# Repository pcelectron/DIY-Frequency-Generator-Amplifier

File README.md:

# DIY-Frequency-Generator-Amplifier

This is a open source frequency generator amplifier capable of delivering up to 1.5 Amps and 28 Vpp at up to 100MHz. It is based on three THS3491 IC's in parallel. The gain of the amplifier stage is fixed at 2, but can be changed by changing the feedback network resistors.
This Repo has the Kicad project files, gerbers, BOM and 3d models of the board and case. Please make a pull request if you have imporvements, which you find to be useful for others.

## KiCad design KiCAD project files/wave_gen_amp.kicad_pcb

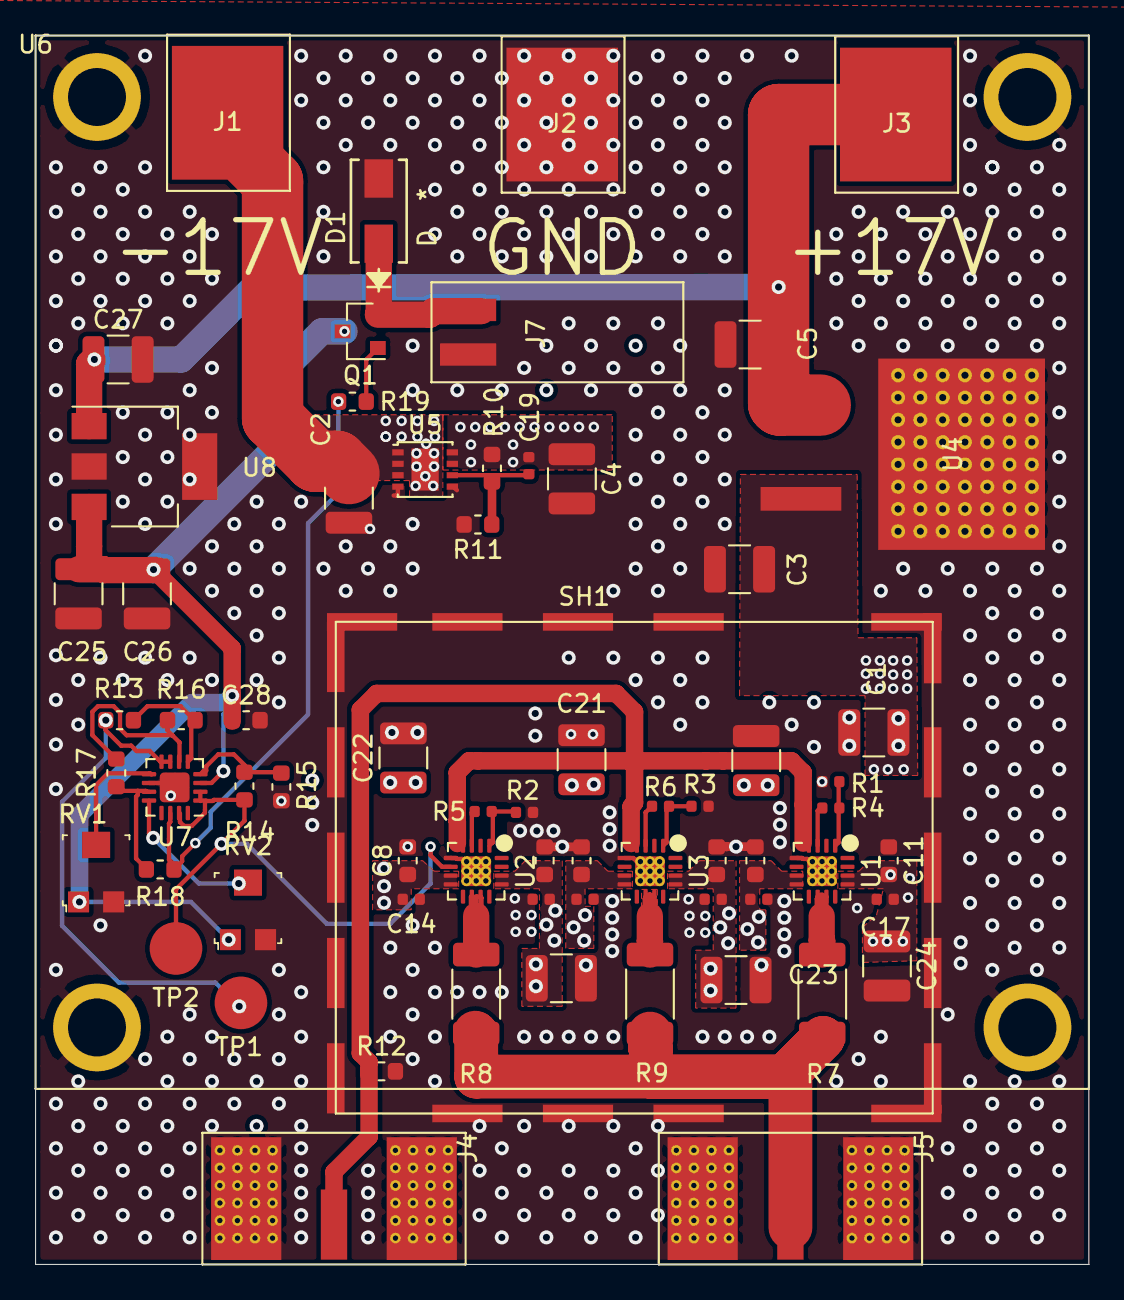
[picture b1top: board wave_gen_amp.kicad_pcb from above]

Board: 2 copper layers, 60.0 x 70.0 mm, 68 parts (0 on the bottom side), 29 nets.

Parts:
C1, C2, C3, C4, C5, C6, C20, C21, C22, C23, C24, C25, C26, C27: 10u; C_1210_3225Metric
C7, C8, C9, C10, C11, C12, C28: 100n; C_0603_1608Metric
C13, C14, C15, C16, C17, C18: 100p; C_0402_1005Metric
C19: 10n; C_0402_1005Metric
D1: D; S1M-13-F
J1: Banana Blue; banana_female_panel_mount
J2: Banana Black; banana_female_panel_mount
J3: Banana Red; banana_female_panel_mount
J4, J5: Conn_Coaxial; VBITE_BNC
J7: FAN; Conn_2x1_smd_horizontal
Q1: DMG2302U; SOT-23
R1, R2, R3, R4, R5, R6: 976R; R_0402_1005Metric
R7, R8, R9: 2.4R; R_2010_5025Metric
R10: 140k; R_0603_1608Metric
R11: 12.4k; R_0603_1608Metric
R12: 50R; R_0603_1608Metric
R13, R14, R17, R19: 1k; R_0603_1608Metric
R15, R16: 30k; R_0603_1608Metric
R18: 3.2k; R_0603_1608Metric
RV1: TJ_REF; Trimpot_3.8mmx3.6mm_TC33X-2-103E
RV2: COMP_REF; Trimpot_3.8mmx3.6mm_TC33X-2-103E
SH1: RF_Shield_One_Piece; SHIELD
TP1, TP2: TestPoint; Testpoint 3mm
U1, U2, U3: THS3491; QFN-16-1EP_3x3mm_P0.5mm_EP1.7x1.7mm_ThermalVias
U4: L7815; TO-263-3
U5: LT3015; DFN-8-1EP_3x3mm_P0.65mm_EP1.55x2.4mm
U6: CU_SKV606021
U7: OPA1679RUM; QFN-16-1EP_3x3mm_P0.5mm_EP1.7x1.7mm
U8: LM2940; SOT-223

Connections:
+12V: C25.1, C26.1, C28.1, Q1.3, RV1.1, RV2.1, U7.3, U8.3
/+15V: C1.1, C3.1, C7.2, C9.2, C11.2, C13.2, C15.2, C17.2, C20.1, C23.1, C24.1, U1.13, U1.14, U2.13, U2.14, U3.13, U3.14, U4.3
/-15V: C4.1, C6.1, C8.1, C10.1, C12.1, C14.1, C16.1, C18.1, C19.1, C21.1, C22.1, R10.1, U1.7, U1.8, U2.7, U2.8, U3.7, U3.8, U5.7, U5.8
/IN: J4.1, R12.1, U1.4, U2.4, U3.4
/OUT: J5.1, R7.1, R8.1, R9.1
/TJ: R14.2, TP2.1, U2.6, U7.1, U7.2, U7.15
/TJ_REF: R13.2, TP1.1, U7.7, U7.8
/VDD: C5.1, C27.1, J3.1, U4.2, U8.1
/VSS: C2.1, J1.1, U5.1, U5.2, U5.3, U5.9
GND: C1.2, C2.2, C3.2, C4.2, C5.2, C6.2, C7.1, C8.2, C9.1, C10.2, C11.1, C12.2, C13.1, C14.2, C15.1, C16.2, C17.1, C18.2, C20.2, C21.2, C22.2, C23.2, C24.2, C25.2, C26.2, C27.2, C28.2, D1.2, J2.1, J4.2, J5.2, J7.1, R1.2, R2.2, R3.2, R11.2, R12.2, R15.1, RV1.3, RV2.3, SH1.1, U1.5, U1.17, U2.5, U2.17, U3.5, U3.17, U4.1, U5.4, U5.5, U6.1, U6.2, U6.3, U6.4, U7.10, U7.17, U8.2, U8.4
unnamed: C19.2, R10.2, R11.1, U5.6
unnamed: D1.1, J7.2, Q1.2
unnamed: Q1.1, R19.1
unnamed: R1.1, R4.1, U1.1
unnamed: R2.1, R5.1, U2.1
unnamed: R3.1, R6.1, U3.1
unnamed: R4.2, U1.3
unnamed: R5.2, U2.3
unnamed: R6.2, U3.3
unnamed: R7.2, U1.10, U1.11
unnamed: R8.2, U2.10, U2.11
unnamed: R9.2, U3.10, U3.11
unnamed: R13.1, R16.2, U7.5
unnamed: R14.1, R15.2, U7.4
unnamed: R16.1, R17.2, U7.6
unnamed: R17.1, R18.2, U7.11
unnamed: R18.1, R19.2, U7.14
unnamed: RV1.2, U7.9
unnamed: RV2.2, U7.12

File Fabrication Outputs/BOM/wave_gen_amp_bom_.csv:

Component;References;Value;Footprint;Quantity Per PCB;digikey order number
1;C7 C8 C9 C10 C11 C12 C28;100n;C_0603_1608Metric;7;C0603C104M5RACTU
2;C13 C14 C15 C16 C17 C18;100p;C_0402_1005Metric;6;CC0402JRNPO9BN101
3;C19;10n;C_0402_1005Metric;1;311-1349-1-ND
4;C1 C2 C3 C4 C5 C6 C20 C21 C22 C23 C24 C25 C26 C27;10u;C_1210_3225Metric;14;1276-3387-1-ND
5;D1;D;S1M-13-F;1;S1M-13-F
6;J1;Banana Blue;banana_female_panel_mount;1;108-0910-001
7;J2;Banana Black;banana_female_panel_mount;1;108-0903-001
8;J3;Banana Red;banana_female_panel_mount;1;108-0902-001
9;J4 J5;Conn_Coaxial;VBITE_BNC;2;031-6233
10;J7;FAN;Conn_2x1_smd_horizontal;1;TSM-102-01-T-SH
11;Q1;DMG2302U;SOT-23;1;DMG2302UK-7
12;R11;12.4k;R_0603_1608Metric;1;RNCP0603FTD12K4CT-ND
13;R10;140k;R_0603_1608Metric;1;RMCF0603FT140KCT-ND
14;R13 R14 R17 R19;1k;R_0603_1608Metric;4;311-1.00KHRCT-ND
15;R7 R8 R9;2.4R;R_2010_5025Metric;3;35022R4FT
16;R18;3.2k;R_0603_1608Metric;1;2019-RN73H1JTTD3201F100CT-ND
17;R15 R16;30k;R_0603_1608Metric;2;311-30.0KHRCT-ND
18;R12;50R;R_0603_1608Metric;1;541-2655-1-ND
19;R1 R2 R3 R4 R5 R6;976R;R_0402_1005Metric;6;RP73PF1E976RBTD
20;RV2;COMP_REF;Trimpot_3.8mmx3.6mm_TC33X-2-103E;1;TC33X-2-103E
21;RV1;TJ_REF;Trimpot_3.8mmx3.6mm_TC33X-2-103E;1;TC33X-2-103E
22;SH1;RF_Shield_One_Piece;SHIELD;1;
23;U6;CU_SKV606021;CU_SKV606021;1;SKV606021-CU
24;U4;L7815;TO-263-3;1;L7815CD2T-TR
25;U8;LM2940;SOT-223;1;LM2940IMP-12/NOPBCT-ND
26;U5;LT3015;DFN-8-1EP_3x3mm_P0.65mm_EP1.55x2.4mm;1;LT3015EDD#PBF
27;U7;OPA1679RUM;QFN-16-1EP_3x3mm_P0.5mm_EP1.7x1.7mm;1;OPA1679IRUMR
28;U1 U2 U3;THS3491;QFN-16-1EP_3x3mm_P0.5mm_EP1.7x1.7mm_ThermalVias;3;THS3491IRGTT

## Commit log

2020-03-14 Create 3D models

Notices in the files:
parts and their libraries:
Copyright 2016 Accelerated Designs. All rights reserved.
